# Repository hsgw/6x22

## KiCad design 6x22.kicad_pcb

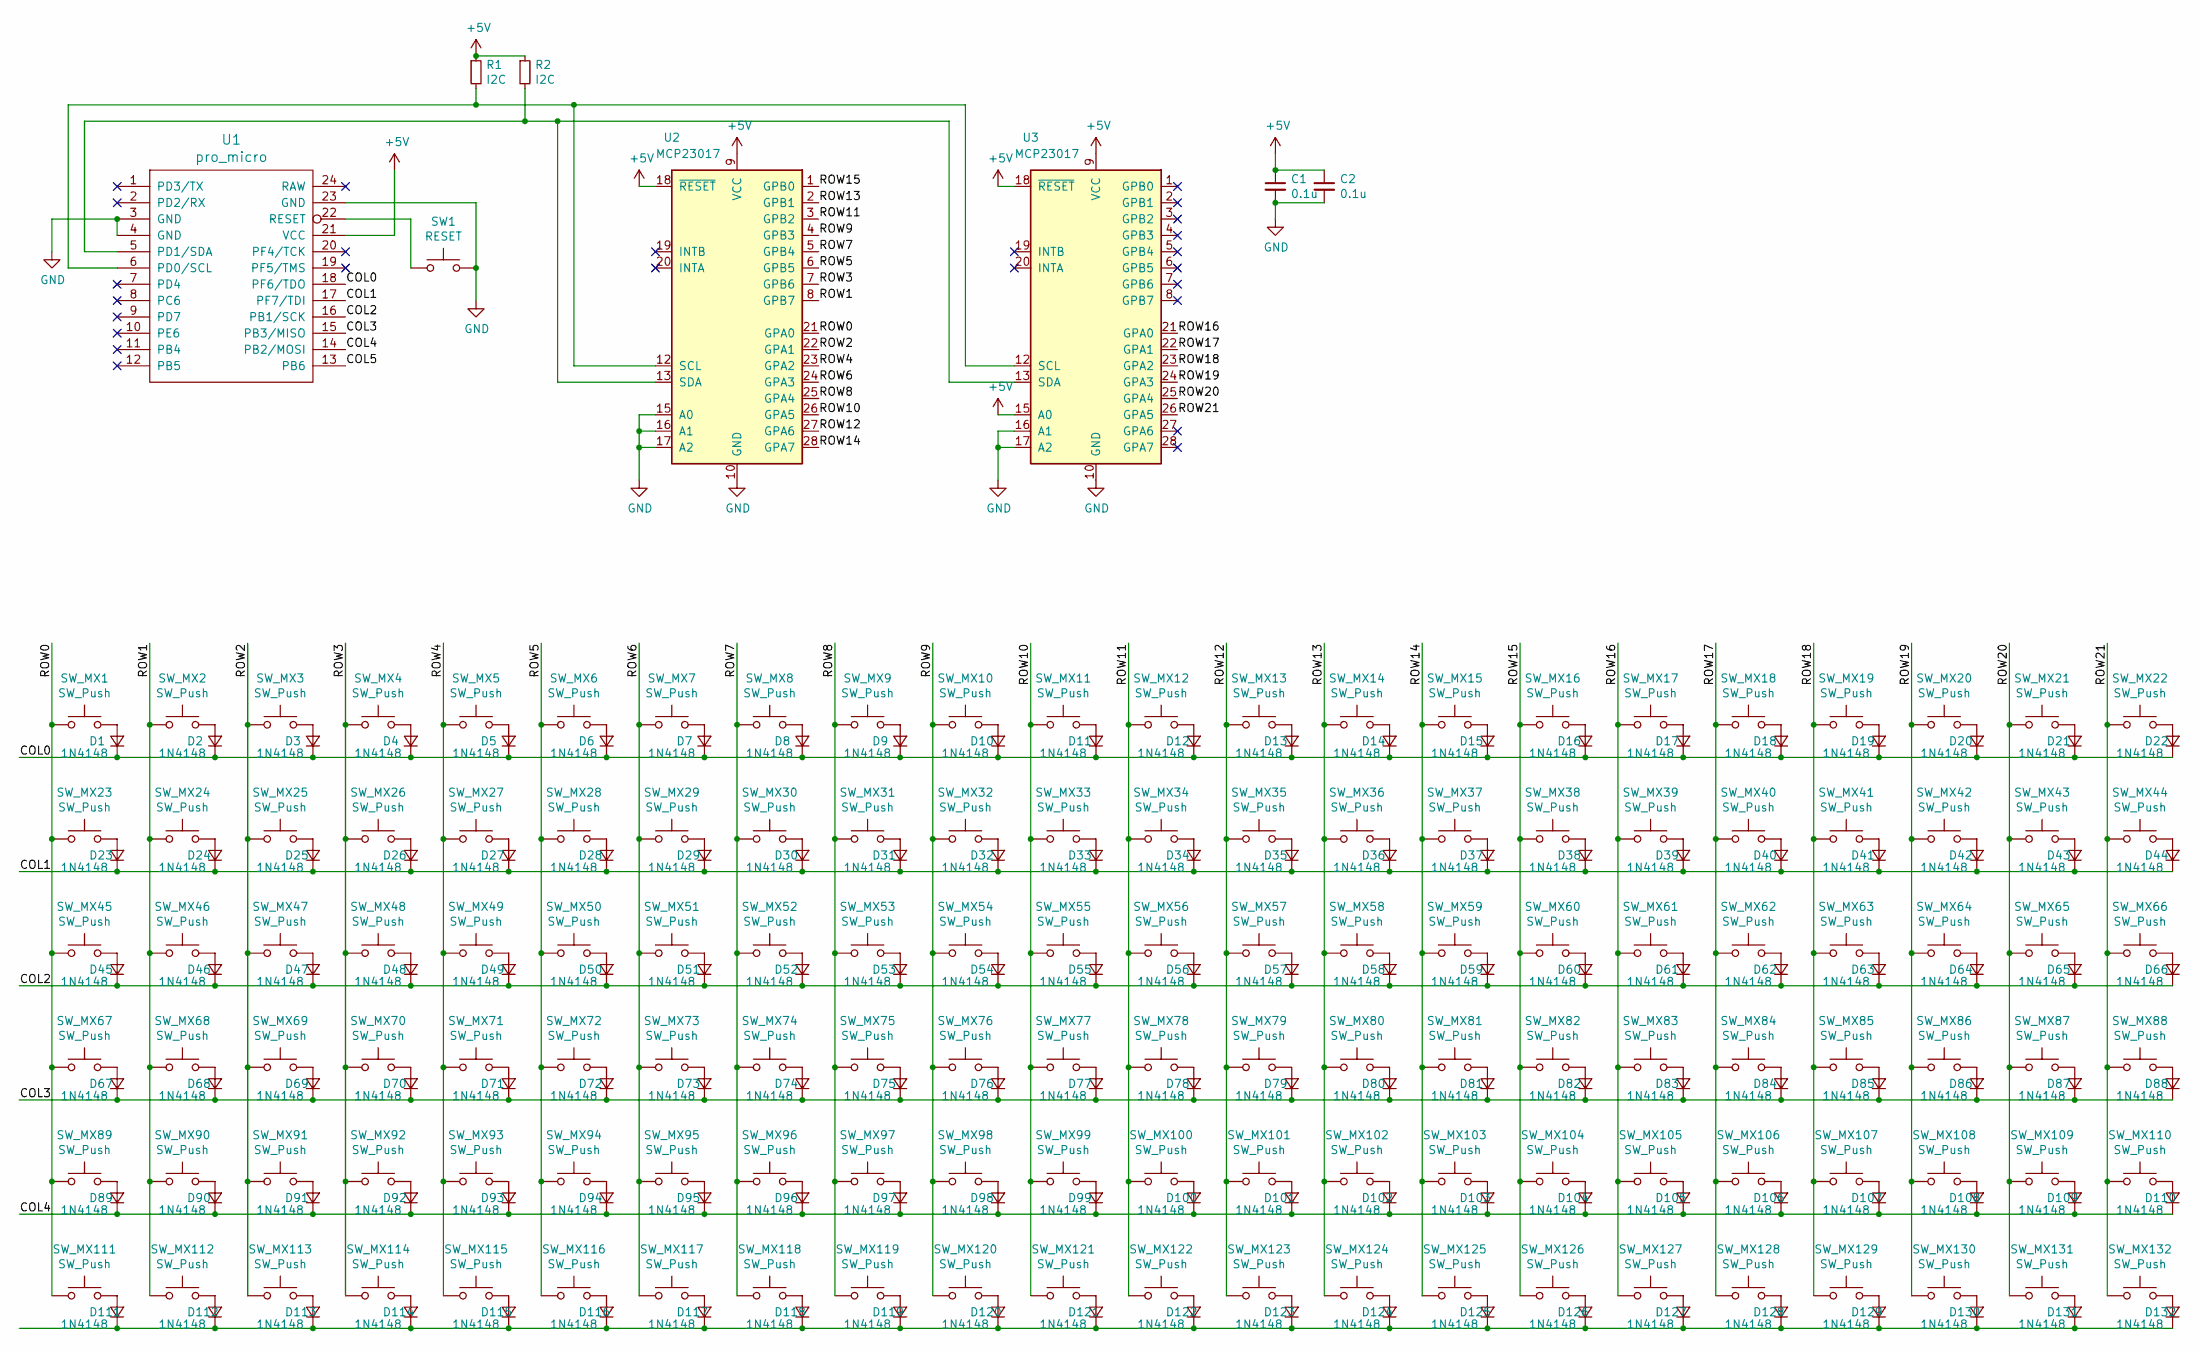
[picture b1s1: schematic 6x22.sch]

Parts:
C1, C2: 0.1u; C_Disc_D3.0mm_W1.6mm_P2.50mm
D1, D2, D3, D4, D5, D6, D7, D8, D9, D10, D11, D12, D13, D14, D15, D16, D17, D18, D19, D20, D21, D22, D23, D24, D25, D26, D27, D28, D29, D30, D31, D32, D33, D34, D35, D36, D37, D38, D39, D40, D41, D42, D43, D44, D45, D46, D47, D48, D49, D50, D51, D52, D53, D54, D55, D56, D57, D58, D59, D60, D61, D62, D63, D64, D65, D66, D67, D68, D69, D70, D71, D72, D73, D74, D75, D76, D77, D78, D79, D80, D81, D82, D83, D84, D85, D86, D87, D88, D89, D90, D91, D92, D93, D94, D95, D96, D97, D98, D99, D100, D101, D102, D103, D104, D105, D106, D107, D108, D109, D110, D111, D112, D113, D114, D115, D116, D117, D118, D119, D120, D121, D122, D123, D124, D125, D126, D127, D128, D129, D130, D131, D132: 1N4148; D_T-1_P5.08mm_Horizontal
R1, R2: I2C; R_Axial_DIN0204_L3.6mm_D1.6mm_P5.08mm_Horizontal
SW1: RESET; SW_Cherry_MX1A_1.00u_PCB
SW_MX1, SW_MX2, SW_MX3, SW_MX4, SW_MX5, SW_MX6, SW_MX7, SW_MX8, SW_MX9, SW_MX10, SW_MX11, SW_MX12, SW_MX13, SW_MX14, SW_MX15, SW_MX16, SW_MX17, SW_MX18, SW_MX19, SW_MX20, SW_MX21, SW_MX22, SW_MX23, SW_MX24, SW_MX25, SW_MX26, SW_MX27, SW_MX28, SW_MX29, SW_MX30, SW_MX31, SW_MX32, SW_MX33, SW_MX34, SW_MX35, SW_MX36, SW_MX37, SW_MX38, SW_MX39, SW_MX40, SW_MX41, SW_MX42, SW_MX43, SW_MX44, SW_MX45, SW_MX46, SW_MX47, SW_MX48, SW_MX49, SW_MX50, SW_MX51, SW_MX52, SW_MX53, SW_MX54, SW_MX55, SW_MX56, SW_MX57, SW_MX58, SW_MX59, SW_MX60, SW_MX61, SW_MX62, SW_MX63, SW_MX64, SW_MX65, SW_MX66, SW_MX67, SW_MX68, SW_MX69, SW_MX70, SW_MX71, SW_MX72, SW_MX73, SW_MX74, SW_MX75, SW_MX76, SW_MX77, SW_MX78, SW_MX79, SW_MX80, SW_MX81, SW_MX82, SW_MX83, SW_MX84, SW_MX85, SW_MX86, SW_MX87, SW_MX88, SW_MX89, SW_MX90, SW_MX91, SW_MX92, SW_MX93, SW_MX94, SW_MX95, SW_MX96, SW_MX97, SW_MX98, SW_MX99, SW_MX100, SW_MX101, SW_MX102, SW_MX103, SW_MX104, SW_MX105, SW_MX106, SW_MX107, SW_MX108, SW_MX109, SW_MX110, SW_MX111, SW_MX112, SW_MX113, SW_MX114, SW_MX115, SW_MX116, SW_MX117, SW_MX118, SW_MX119, SW_MX120, SW_MX121, SW_MX122, SW_MX123, SW_MX124, SW_MX125, SW_MX126, SW_MX127, SW_MX128, SW_MX129, SW_MX130, SW_MX131, SW_MX132: SW_Push; SW_Cherry_MX1A_1.00u_PCB
U1: pro_micro; BOARD_Pro_Micro
U2, U3: MCP23017; DIP-28_W7.62mm

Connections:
+5V: C1.1, C2.1, R1.1, R2.1, U1.21 (VCC), U2.9 (VCC), U2.18 (~RESET), U3.9 (VCC), U3.15 (A0), U3.18 (~RESET)
/COL0: D1.1 (K), D2.1 (K), D3.1 (K), D4.1 (K), D5.1 (K), D6.1 (K), D7.1 (K), D8.1 (K), D9.1 (K), D10.1 (K), D11.1 (K), D12.1 (K), D13.1 (K), D14.1 (K), D15.1 (K), D16.1 (K), D17.1 (K), D18.1 (K), D19.1 (K), D20.1 (K), D21.1 (K), D22.1 (K), U1.18 (PF6/TDO)
/COL1: D23.1 (K), D24.1 (K), D25.1 (K), D26.1 (K), D27.1 (K), D28.1 (K), D29.1 (K), D30.1 (K), D31.1 (K), D32.1 (K), D33.1 (K), D34.1 (K), D35.1 (K), D36.1 (K), D37.1 (K), D38.1 (K), D39.1 (K), D40.1 (K), D41.1 (K), D42.1 (K), D43.1 (K), D44.1 (K), U1.17 (PF7/TDI)
/COL2: D45.1 (K), D46.1 (K), D47.1 (K), D48.1 (K), D49.1 (K), D50.1 (K), D51.1 (K), D52.1 (K), D53.1 (K), D54.1 (K), D55.1 (K), D56.1 (K), D57.1 (K), D58.1 (K), D59.1 (K), D60.1 (K), D61.1 (K), D62.1 (K), D63.1 (K), D64.1 (K), D65.1 (K), D66.1 (K), U1.16 (PB1/SCK)
/COL3: D67.1 (K), D68.1 (K), D69.1 (K), D70.1 (K), D71.1 (K), D72.1 (K), D73.1 (K), D74.1 (K), D75.1 (K), D76.1 (K), D77.1 (K), D78.1 (K), D79.1 (K), D80.1 (K), D81.1 (K), D82.1 (K), D83.1 (K), D84.1 (K), D85.1 (K), D86.1 (K), D87.1 (K), D88.1 (K), U1.15 (PB3/MISO)
/COL4: D89.1 (K), D90.1 (K), D91.1 (K), D92.1 (K), D93.1 (K), D94.1 (K), D95.1 (K), D96.1 (K), D97.1 (K), D98.1 (K), D99.1 (K), D100.1 (K), D101.1 (K), D102.1 (K), D103.1 (K), D104.1 (K), D105.1 (K), D106.1 (K), D107.1 (K), D108.1 (K), D109.1 (K), D110.1 (K), U1.14 (PB2/MOSI)
/COL5: U1.13 (PB6)
/ROW0: SW_MX1.1, SW_MX23.1, SW_MX45.1, SW_MX67.1, SW_MX89.1, SW_MX111.1, U2.21 (GPA0)
/ROW1: SW_MX2.1, SW_MX24.1, SW_MX46.1, SW_MX68.1, SW_MX90.1, SW_MX112.1, U2.8 (GPB7)
/ROW2: SW_MX3.1, SW_MX25.1, SW_MX47.1, SW_MX69.1, SW_MX91.1, SW_MX113.1, U2.22 (GPA1)
/ROW3: SW_MX4.1, SW_MX26.1, SW_MX48.1, SW_MX70.1, SW_MX92.1, SW_MX114.1, U2.7 (GPB6)
/ROW4: SW_MX5.1, SW_MX27.1, SW_MX49.1, SW_MX71.1, SW_MX93.1, SW_MX115.1, U2.23 (GPA2)
/ROW5: SW_MX6.1, SW_MX28.1, SW_MX50.1, SW_MX72.1, SW_MX94.1, SW_MX116.1, U2.6 (GPB5)
/ROW6: SW_MX7.1, SW_MX29.1, SW_MX51.1, SW_MX73.1, SW_MX95.1, SW_MX117.1, U2.24 (GPA3)
/ROW7: SW_MX8.1, SW_MX30.1, SW_MX52.1, SW_MX74.1, SW_MX96.1, SW_MX118.1, U2.5 (GPB4)
/ROW8: SW_MX9.1, SW_MX31.1, SW_MX53.1, SW_MX75.1, SW_MX97.1, SW_MX119.1, U2.25 (GPA4)
/ROW9: SW_MX10.1, SW_MX32.1, SW_MX54.1, SW_MX76.1, SW_MX98.1, SW_MX120.1, U2.4 (GPB3)
/ROW10: SW_MX11.1, SW_MX33.1, SW_MX55.1, SW_MX77.1, SW_MX99.1, SW_MX121.1, U2.26 (GPA5)
/ROW11: SW_MX12.1, SW_MX34.1, SW_MX56.1, SW_MX78.1, SW_MX100.1, SW_MX122.1, U2.3 (GPB2)
/ROW12: SW_MX13.1, SW_MX35.1, SW_MX57.1, SW_MX79.1, SW_MX101.1, SW_MX123.1, U2.27 (GPA6)
/ROW13: SW_MX14.1, SW_MX36.1, SW_MX58.1, SW_MX80.1, SW_MX102.1, SW_MX124.1, U2.2 (GPB1)
/ROW14: SW_MX15.1, SW_MX37.1, SW_MX59.1, SW_MX81.1, SW_MX103.1, SW_MX125.1, U2.28 (GPA7)
/ROW15: SW_MX16.1, SW_MX38.1, SW_MX60.1, SW_MX82.1, SW_MX104.1, SW_MX126.1, U2.1 (GPB0)
/ROW16: SW_MX17.1, SW_MX39.1, SW_MX61.1, SW_MX83.1, SW_MX105.1, SW_MX127.1, U3.21 (GPA0)
/ROW17: SW_MX18.1, SW_MX40.1, SW_MX62.1, SW_MX84.1, SW_MX106.1, SW_MX128.1, U3.22 (GPA1)
/ROW18: SW_MX19.1, SW_MX41.1, SW_MX63.1, SW_MX85.1, SW_MX107.1, SW_MX129.1, U3.23 (GPA2)
/ROW19: SW_MX20.1, SW_MX42.1, SW_MX64.1, SW_MX86.1, SW_MX108.1, SW_MX130.1, U3.24 (GPA3)
/ROW20: SW_MX21.1, SW_MX43.1, SW_MX65.1, SW_MX87.1, SW_MX109.1, SW_MX131.1, U3.25 (GPA4)
/ROW21: SW_MX22.1, SW_MX44.1, SW_MX66.1, SW_MX88.1, SW_MX110.1, SW_MX132.1, U3.26 (GPA5)
GND: C1.2, C2.2, SW1.2, U1.3 (GND), U1.4 (GND), U1.23 (GND), U2.10 (GND), U2.15 (A0), U2.16 (A1), U2.17 (A2), U3.10 (GND), U3.16 (A1), U3.17 (A2)
unnamed: D1.2 (A), SW_MX1.2
unnamed: D2.2 (A), SW_MX2.2
unnamed: D3.2 (A), SW_MX3.2
unnamed: D4.2 (A), SW_MX4.2
unnamed: D5.2 (A), SW_MX5.2
unnamed: D6.2 (A), SW_MX6.2
unnamed: D7.2 (A), SW_MX7.2
unnamed: D8.2 (A), SW_MX8.2
unnamed: D9.2 (A), SW_MX9.2
unnamed: D10.2 (A), SW_MX10.2
unnamed: D11.2 (A), SW_MX11.2
unnamed: D12.2 (A), SW_MX12.2
unnamed: D13.2 (A), SW_MX13.2
unnamed: D14.2 (A), SW_MX14.2
unnamed: D15.2 (A), SW_MX15.2
unnamed: D16.2 (A), SW_MX16.2
unnamed: D17.2 (A), SW_MX17.2
unnamed: D18.2 (A), SW_MX18.2
unnamed: D19.2 (A), SW_MX19.2
unnamed: D20.2 (A), SW_MX20.2
unnamed: D21.2 (A), SW_MX21.2
unnamed: D22.2 (A), SW_MX22.2
unnamed: D23.2 (A), SW_MX23.2
unnamed: D24.2 (A), SW_MX24.2
unnamed: D25.2 (A), SW_MX25.2
unnamed: D26.2 (A), SW_MX26.2
unnamed: D27.2 (A), SW_MX27.2
unnamed: D28.2 (A), SW_MX28.2
unnamed: D29.2 (A), SW_MX29.2
unnamed: D30.2 (A), SW_MX30.2
unnamed: D31.2 (A), SW_MX31.2
unnamed: D32.2 (A), SW_MX32.2
unnamed: D33.2 (A), SW_MX33.2
unnamed: D34.2 (A), SW_MX34.2
unnamed: D35.2 (A), SW_MX35.2
unnamed: D36.2 (A), SW_MX36.2
unnamed: D37.2 (A), SW_MX37.2
unnamed: D38.2 (A), SW_MX38.2
unnamed: D39.2 (A), SW_MX39.2
unnamed: D40.2 (A), SW_MX40.2
unnamed: D41.2 (A), SW_MX41.2
unnamed: D42.2 (A), SW_MX42.2
unnamed: D43.2 (A), SW_MX43.2
unnamed: D44.2 (A), SW_MX44.2
unnamed: D45.2 (A), SW_MX45.2
unnamed: D46.2 (A), SW_MX46.2
unnamed: D47.2 (A), SW_MX47.2
unnamed: D48.2 (A), SW_MX48.2
unnamed: D49.2 (A), SW_MX49.2
unnamed: D50.2 (A), SW_MX50.2
unnamed: D51.2 (A), SW_MX51.2
unnamed: D52.2 (A), SW_MX52.2
unnamed: D53.2 (A), SW_MX53.2
unnamed: D54.2 (A), SW_MX54.2
unnamed: D55.2 (A), SW_MX55.2
unnamed: D56.2 (A), SW_MX56.2
unnamed: D57.2 (A), SW_MX57.2
unnamed: D58.2 (A), SW_MX58.2
unnamed: D59.2 (A), SW_MX59.2
unnamed: D60.2 (A), SW_MX60.2
unnamed: D61.2 (A), SW_MX61.2
unnamed: D62.2 (A), SW_MX62.2
unnamed: D63.2 (A), SW_MX63.2
unnamed: D64.2 (A), SW_MX64.2
unnamed: D65.2 (A), SW_MX65.2
unnamed: D66.2 (A), SW_MX66.2
unnamed: D67.2 (A), SW_MX67.2
unnamed: D68.2 (A), SW_MX68.2
unnamed: D69.2 (A), SW_MX69.2
unnamed: D70.2 (A), SW_MX70.2
unnamed: D71.2 (A), SW_MX71.2
unnamed: D72.2 (A), SW_MX72.2
unnamed: D73.2 (A), SW_MX73.2
unnamed: D74.2 (A), SW_MX74.2
unnamed: D75.2 (A), SW_MX75.2
unnamed: D76.2 (A), SW_MX76.2
unnamed: D77.2 (A), SW_MX77.2
unnamed: D78.2 (A), SW_MX78.2
unnamed: D79.2 (A), SW_MX79.2
unnamed: D80.2 (A), SW_MX80.2
unnamed: D81.2 (A), SW_MX81.2
unnamed: D82.2 (A), SW_MX82.2
unnamed: D83.2 (A), SW_MX83.2
unnamed: D84.2 (A), SW_MX84.2
unnamed: D85.2 (A), SW_MX85.2
unnamed: D86.2 (A), SW_MX86.2
unnamed: D87.2 (A), SW_MX87.2
unnamed: D88.2 (A), SW_MX88.2
unnamed: D89.2 (A), SW_MX89.2
unnamed: D90.2 (A), SW_MX90.2
unnamed: D91.2 (A), SW_MX91.2
unnamed: D92.2 (A), SW_MX92.2
unnamed: D93.2 (A), SW_MX93.2
unnamed: D94.2 (A), SW_MX94.2
unnamed: D95.2 (A), SW_MX95.2
unnamed: D96.2 (A), SW_MX96.2
unnamed: D97.2 (A), SW_MX97.2
unnamed: D98.2 (A), SW_MX98.2
unnamed: D99.2 (A), SW_MX99.2
unnamed: D100.2 (A), SW_MX100.2
unnamed: D101.2 (A), SW_MX101.2
unnamed: D102.2 (A), SW_MX102.2
unnamed: D103.2 (A), SW_MX103.2
unnamed: D104.2 (A), SW_MX104.2
unnamed: D105.2 (A), SW_MX105.2
unnamed: D106.2 (A), SW_MX106.2
unnamed: D107.2 (A), SW_MX107.2
unnamed: D108.2 (A), SW_MX108.2
unnamed: D109.2 (A), SW_MX109.2
unnamed: D110.2 (A), SW_MX110.2
unnamed: D111.1 (K), D112.1 (K), D113.1 (K), D114.1 (K), D115.1 (K), D116.1 (K), D117.1 (K), D118.1 (K), D119.1 (K), D120.1 (K), D121.1 (K), D122.1 (K), D123.1 (K), D124.1 (K), D125.1 (K), D126.1 (K), D127.1 (K), D128.1 (K), D129.1 (K), D130.1 (K), D131.1 (K), D132.1 (K)
unnamed: D111.2 (A), SW_MX111.2
unnamed: D112.2 (A), SW_MX112.2
unnamed: D113.2 (A), SW_MX113.2
unnamed: D114.2 (A), SW_MX114.2
unnamed: D115.2 (A), SW_MX115.2
unnamed: D116.2 (A), SW_MX116.2
unnamed: D117.2 (A), SW_MX117.2
unnamed: D118.2 (A), SW_MX118.2
unnamed: D119.2 (A), SW_MX119.2
unnamed: D120.2 (A), SW_MX120.2
unnamed: D121.2 (A), SW_MX121.2
unnamed: D122.2 (A), SW_MX122.2
unnamed: D123.2 (A), SW_MX123.2
unnamed: D124.2 (A), SW_MX124.2
unnamed: D125.2 (A), SW_MX125.2
unnamed: D126.2 (A), SW_MX126.2
unnamed: D127.2 (A), SW_MX127.2
unnamed: D128.2 (A), SW_MX128.2
unnamed: D129.2 (A), SW_MX129.2
unnamed: D130.2 (A), SW_MX130.2
unnamed: D131.2 (A), SW_MX131.2
unnamed: D132.2 (A), SW_MX132.2
unnamed: R1.2, U1.6 (PD0/SCL), U2.12 (SCL), U3.12 (SCL)
unnamed: R2.2, U1.5 (PD1/SDA), U2.13 (SDA), U3.13 (SDA)
unnamed: SW1.1, U1.22 (RESET)

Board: 2 copper layers, 272 parts (0 on the bottom side), 165 nets, no tracks yet.

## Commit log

2019-10-05 I don't know
